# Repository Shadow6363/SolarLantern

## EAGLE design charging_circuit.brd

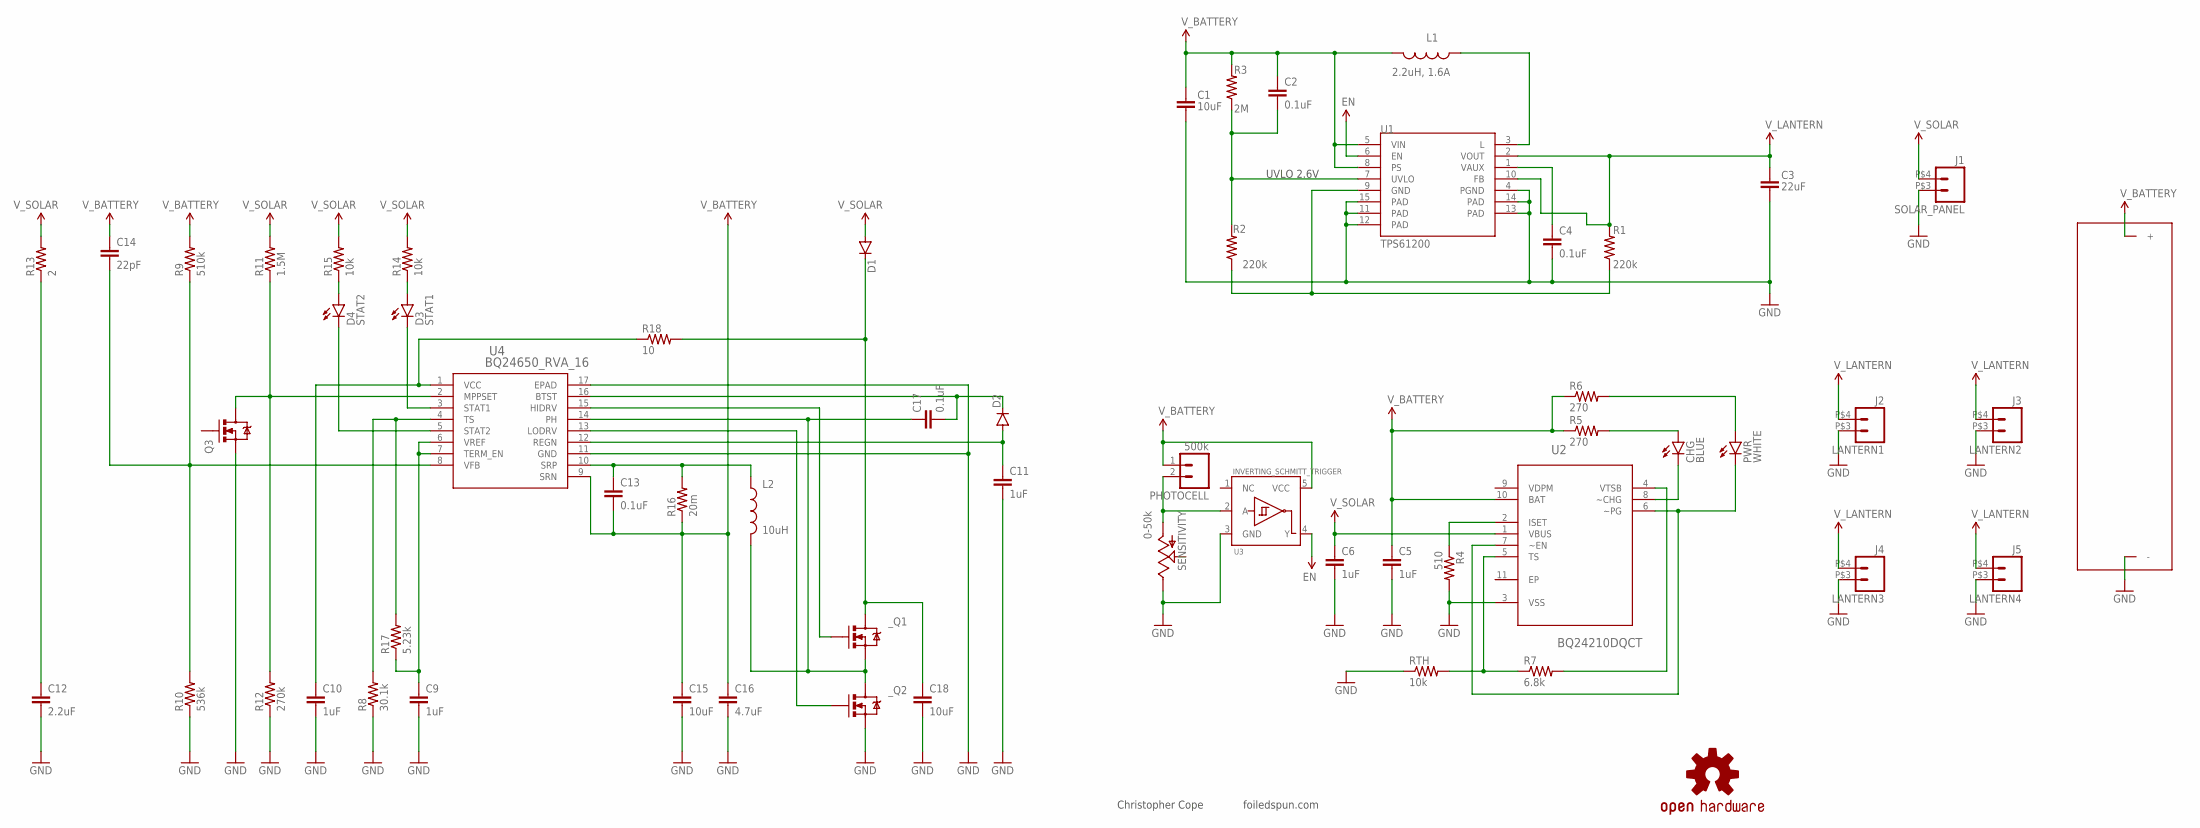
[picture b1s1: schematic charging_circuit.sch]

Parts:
C1: 10uF; 1206
C2, C4: 0.1uF; 0402-CAP
C3: 22uF; 0805
C5, C6: 1uF; 0805
C9, C10, C11: 1uF; 0402-CAP
C12: 2.2uF; 0402-CAP
C13, C17: 0.1uF; 0805
C14: 22pF; 0603-CAP
C15, C18: 10uF; 1210
C16: 4.7uF; 1210
CHG: BLUE; LED-0603
D1: DIODEPDS1040; POWERDI-5
D2: DIODESOT23; SOT23-3
D3: STAT1; LED-0603
D4: STAT2; LED-0603
L1: 2.2uH, 1.6A; 1210
L2: 10uH; IHLP-2525CZ-01
LANTERN1: J2; 2-1445100-2
LANTERN2: J3; 2-1445100-2
LANTERN3: J4; 2-1445100-2
LANTERN4: J5; 2-1445100-2
LOGO2: OSHW-LOGOL; OSHW-LOGO-L
PHOTOCELL: 500k; 1X02_SMD
PWR: WHITE; LED-0603
Q3: MOSFET-NCHANNEL; SOT23-3
R1, R2: 220k; 0402-RES
R3: 2M; 0402-RES
R4: 510; 0402-RES
R5, R6: 270; 0402-RES
R7: 6.8k; 0402-RES
R8: 30.1k; 0402-RES
R9: 510k; 0402-RES
R10: 536k; 0402-RES
R11: 1.5M; 0402-RES
R12: 270k; 0402-RES
R13: 2; 0402-RES
R14, R15: 10k; 0402-RES
R16: 20m; 1206
R17: 5.23k; 0402-RES
R18: 10; 1206
RTH: 10k; 0402-RES
SENSITIVITY: 0-50k; TRIM_POT-SMD
SOLAR_PANEL: J1; 2-1445100-2
U1: TPS61200; QFN-10_PAD
U2: BQ24210DQCT; SON50P200X300X80-11N
U3: INVERTING_SCHMITT_TRIGGER; SC-70-5(DCK)
U4: BQ24650_RVA_16; RVA16_2P14X2P14
U$1: 18650-HOLDER; 18650
_: MOSFET-DUAL_NCHANNEL; POWERPAK_SO-8

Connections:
EN: U1.6 (EN), U3.4 (Y)
GND: C1.2, C3.2, C4.2, C5.2, C6.2, C9.2, C10.2, C11.2, C12.2, C15.2, C16.2, C18.2, LANTERN1.P$3 (2), LANTERN2.P$3 (2), LANTERN3.P$3 (2), LANTERN4.P$3 (2), Q3.2 (S), R4.2, R8.1, R10.1, R12.1, RTH.1, SENSITIVITY.P$3 (E), SOLAR_PANEL.P$3 (2), U1.4 (PGND), U1.11 (PAD), U1.12 (PAD), U1.13 (PAD), U1.14 (PAD), U1.15 (PAD), U2.3 (VSS), U3.3 (GND), U4.11 (GND), U4.17 (EPAD), U$1.-, _.P$3$S2 (S)
GND1: R1.1, R2.1, U1.9 (GND)
unnamed: C4.1, U1.1 (VAUX)
unnamed: L1.1, U1.3 (L)
unnamed: CHG.C, U2.8 (~CHG)
unnamed: PWR.C, U2.6 (~PG), U2.7 (~EN)
unnamed: CHG.A, R5.2
unnamed: PWR.A, R6.2
unnamed: PHOTOCELL.2, SENSITIVITY.P$1 (A), U3.2 (A)
unnamed: R4.1, U2.2 (ISET)
unnamed: R7.2, U2.4 (VTSB)
unnamed: R7.1, RTH.2, U2.5 (TS)
unnamed: C10.1, R18.1, U4.1 (VCC)
unnamed: C14.2, R9.1, R10.2, U4.8 (VFB)
unnamed: C11.1, D2.1 (A), U4.12 (REGN)
unnamed: Q3.3 (D), R11.1, R12.2, U4.2 (MPPSET)
unnamed: C12.1, R13.1
unnamed: D3.C, U4.3 (STAT1)
unnamed: D4.C, U4.5 (STAT2)
unnamed: D4.A, R15.1
unnamed: D3.A, R14.1
unnamed: R8.2, R17.2, U4.4 (TS)
unnamed: C17.2, D2.3 (C), U4.16 (BTST)
unnamed: C17.1, L2.P$2 (2), U4.14 (PH), _.P$1$S1 (S), _.P$5$D2 (D), _.P$6$D2 (D), _.P$D2 (D)
unnamed: C9.1, R17.1, U4.6 (VREF), U4.7 (TERM_EN)
unnamed: U4.13 (LODRV), _.P$4$G2 (G)
unnamed: U4.15 (HIDRV), _.P$2$G1 (G)
unnamed: C18.1, D1.P$3 (C), R18.2, _.P$7$D1 (D), _.P$8$D1 (D), _.P$D1 (D)
unnamed: C13.1, L2.P$1 (1), R16.2, U4.10 (SRP)
UVLO: C2.2, R2.2, R3.1, U1.7 (UVLO)
V_BATTERY: C1.1, C2.1, C5.1, C13.2, C14.1, C15.1, C16.1, L1.2, PHOTOCELL.1, R3.2, R5.1, R6.1, R9.2, R16.1, U1.5 (VIN), U1.8 (PS), U2.10 (BAT), U3.5 (VCC), U4.9 (SRN), U$1.+
V_LANTERN: C3.1, LANTERN1.P$4 (1), LANTERN2.P$4 (1), LANTERN3.P$4 (1), LANTERN4.P$4 (1), R1.2, U1.2 (VOUT), U1.10 (FB)
V_SOLAR: C6.1, D1.P$1 (A), D1.P$2 (A), R11.2, R13.2, R14.2, R15.2, SOLAR_PANEL.P$4 (1), U2.1 (VBUS)

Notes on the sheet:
UVLO 2.6V
Christopher Cope
foiledspun.com

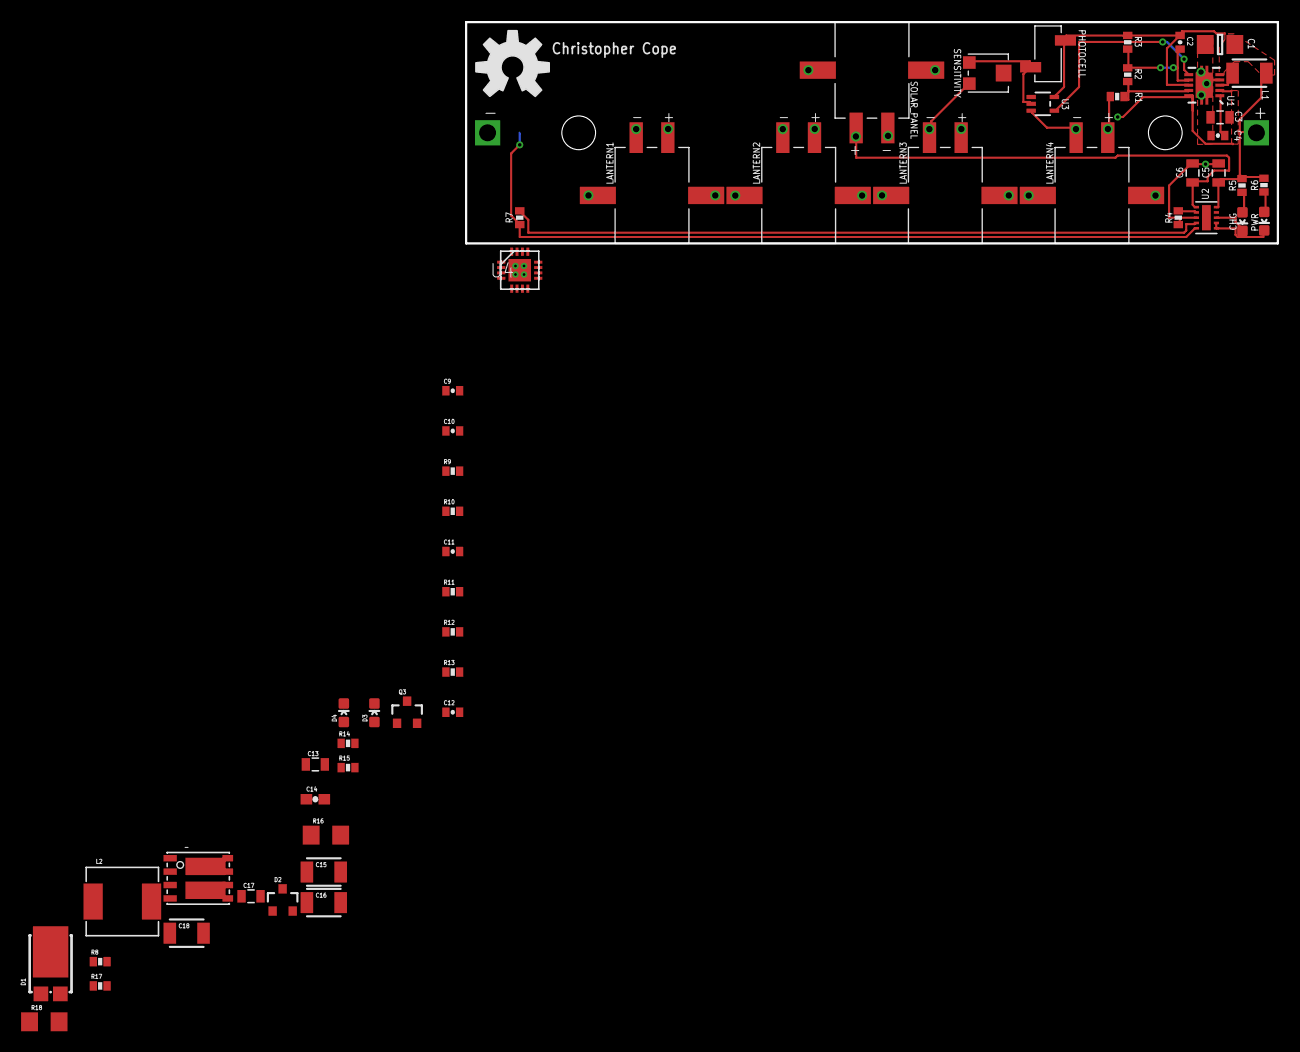
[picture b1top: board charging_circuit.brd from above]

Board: 2 copper layers, 77.0 x 21.0 mm, 58 parts (1 on the bottom side), 34 nets.

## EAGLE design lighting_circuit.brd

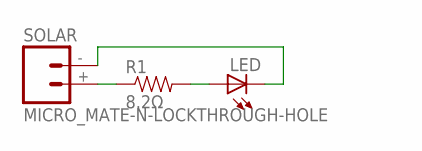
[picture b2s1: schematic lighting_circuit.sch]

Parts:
LED: LED; PLCC6
R1: 8.2Ω; 1206
SOLAR: MICRO_MATE-N-LOCKTHROUGH-HOLE; 2-1445093-2

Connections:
unnamed: LED.1 (A), LED.2 (A), LED.3 (A), R1.2
unnamed: R1.1, SOLAR.+ (1)
unnamed: LED.4 (C), LED.5 (C), LED.6 (C), SOLAR.- (2)

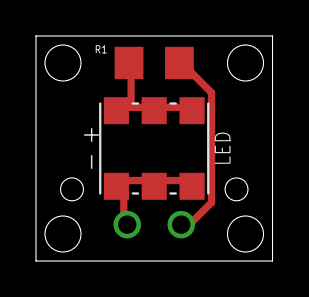
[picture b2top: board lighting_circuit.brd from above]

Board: 2 copper layers, 13.1 x 12.5 mm, 3 parts (1 on the bottom side), 3 nets.

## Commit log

2014-07-27 Initial commit?

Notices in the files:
parts and their libraries:
SparkFun-Resistors: Licensing: CC v3.0 Share-Alike You are welcome to use this library for commercial purposes.
SparkFun-Passives: Licensing: Creative Commons ShareAlike 4.0 International - https://creativecommons.org/licenses/by-sa/4.0
